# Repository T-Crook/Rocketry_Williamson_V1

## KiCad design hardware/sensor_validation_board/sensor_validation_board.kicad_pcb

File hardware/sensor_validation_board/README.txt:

This file documents the macro decisions related to the MEMS sensor validation for the Williamson rocket v1 flight computer.

On a previous flight computer project at university we ran into major issues with the reliability of both the barometer (BMP585) and IMU (LSM6DSO32). We believe this was an issue with our soldering/assembly. This sensor validation board is designed to test the flight computer chips before we commit to sensor selection. 

Requirements:

- The chips must be able to run off 3V3 logic to simplify power requirements

- The chip which is finally selected must withstand soldering in a predictable and consistent way. 

- The chip must be able to be soldered at home/university. 

Datasheets for trial chips:

IMU:

(slightly older version of one used for uni project)
https://www.digikey.co.nz/en/products/detail/stmicroelectronics/LSM6DSLTR/6192804

- I would also like to try using an MPU6050, since they have been so widely used. Even though they are quite old. No stock at digikey however.

Barometer:

(BPS space used this)
https://www.digikey.co.nz/en/products/detail/te-connectivity-measurement-specialties/MS561101BA03-50/5277445

(same as university selection, BMP585)
https://www.digikey.co.nz/en/products/detail/bosch-sensortec/BMP585/19522589

(popular in industry, BMP581)
https://www.digikey.co.nz/en/products/detail/bosch-sensortec/BMP581/16036134

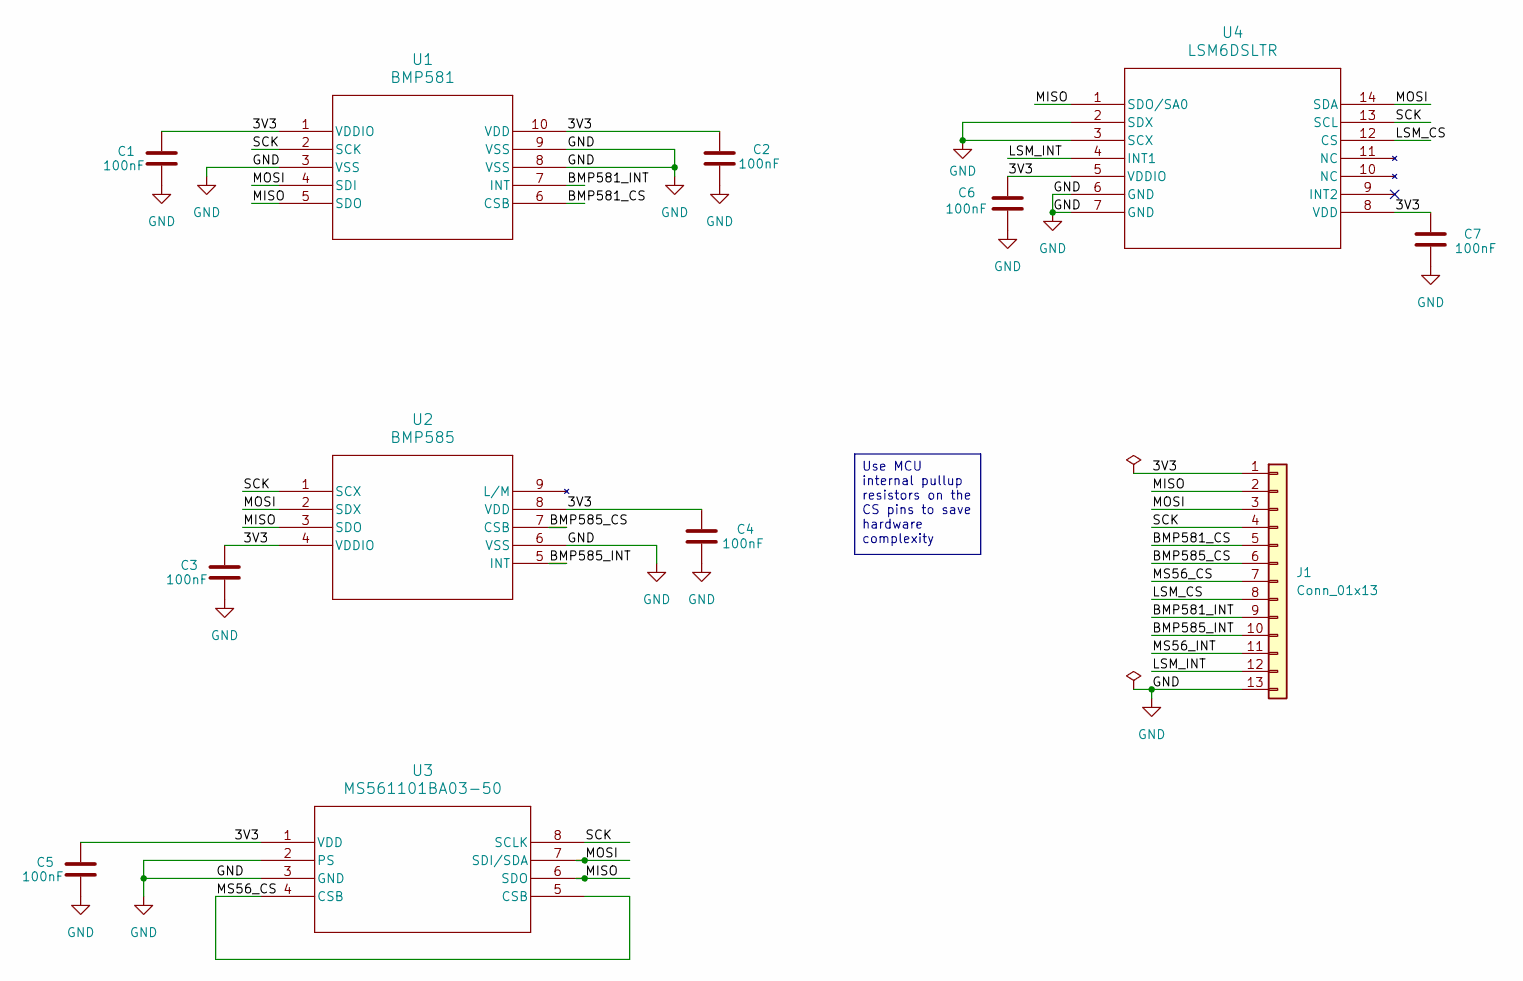
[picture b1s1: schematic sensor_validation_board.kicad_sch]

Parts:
C1, C2, C3, C4, C5, C6, C7: 100nF; C_0805_2012Metric
J1: Conn_01x13; PinHeader_1x13_P2.54mm_Vertical
U1: BMP581; QFN10_BMP581_BOS
U2: BMP585; LGA9_BMP585_BOS
U3: MS561101BA03-50; SON8_MS5611_TEC
U4: LSM6DSLTR; QFN_6DSLTR_STM

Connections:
/3V3: C1.1, C2.1, C3.1, C4.1, C5.1, C6.1, C7.1, J1.1, U1.1 (VDDIO), U1.10 (VDD), U2.4 (VDDIO), U2.8 (VDD), U3.1 (VDD), U4.5 (VDDIO), U4.8 (VDD)
/BMP581_CS: J1.5, U1.6 (CSB)
/BMP581_INT: J1.9, U1.7 (INT)
/BMP585_CS: J1.6, U2.7 (CSB)
/BMP585_INT: J1.10, U2.5 (INT)
/LSM_CS: J1.8, U4.12 (CS)
/LSM_INT: J1.12, U4.4 (INT1)
/MISO: J1.2, U1.5 (SDO), U2.3 (SDO), U3.6 (SDO), U4.1 (SDO/SA0)
/MOSI: J1.3, U1.4 (SDI), U2.2 (SDX), U3.7 (SDI/SDA), U4.14 (SDA)
/MS56_CS: J1.7, U3.4 (CSB), U3.5 (CSB)
/MS56_INT: J1.11
/SCK: J1.4, U1.2 (SCK), U2.1 (SCX), U3.8 (SCLK), U4.13 (SCL)
GND: C1.2, C2.2, C3.2, C4.2, C5.2, C6.2, C7.2, J1.13, U1.3 (VSS), U1.8 (VSS), U1.9 (VSS), U2.6 (VSS), U3.2 (PS), U3.3 (GND), U4.2 (SDX), U4.3 (SCX), U4.6 (GND), U4.7 (GND)

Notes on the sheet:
Use MCU internal pullup resistors on the CS pins to save hardware complexity

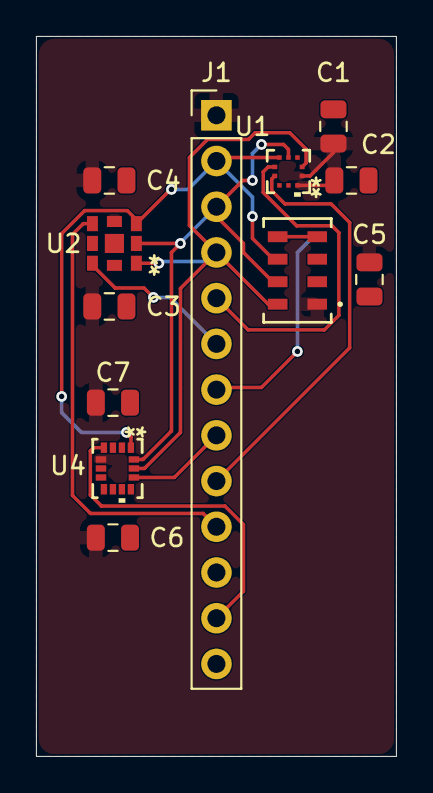
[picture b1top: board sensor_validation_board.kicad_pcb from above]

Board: 2 copper layers, 20.0 x 40.0 mm, 12 parts (0 on the bottom side), 12 nets.
